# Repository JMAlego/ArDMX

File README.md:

# ArDMX

*DMX512 Interface Shield*

## Introduction

Following the creation of [AVR-DMX](https://github.com/JMAlego/AVR-DMX) for Arduino, I decided that my first foray into circuit board design should be the creation of a shield to work with AVR-DMX to allow proper interfacing of an Arduino to a DMX network.

**NB**: I have yet to actually get one of these made so who knows if it works, it's based on a perfboarded design that works correctly though.

## DIP Switches

- 120Ω Termination:
- Mode (only enable one unless you want a short):
  - Always Receive: Pull-down
  - Always Transmit: Pull-up
  - Software Control: Connect to pin 2
- Read Enable: Connect read output to pin 8
- Status LED Enable: Connect status LED to pin 9

## Optional Components

- D2 & D3 are only required for max voltage clamping on the DMX bus, if you're not worried about over/under-voltage then don't bother with them.
- SW2 & R1 are optional if you don't want 120Ω termination.
- J2 is not required if you don't want to use the outputs without the XLR connector.
- J1 is not required if you plan to use J2 to connect to the DMX network.
- Smoothing caps C1 & C2 are also optional if you're sure your input supply will be sufficiently smooth.
- D4 & R5 are optional if you don't want the power LED.
- Similarly, D1 & R4 are optional if you don't want the status LED.

## Rough Costing

It should be possible to build for around £10 or less (though you may need to make a few). You'll find the most expensive part is the Neutrik NC5FAH-DA (or compatible) XLR 5-pin connector.

As of revision 1.1 a cheaper option of using the 3-pin XLR Neutrik NC3FAH1-DA connector which the board now also supports.

## License

Hardware designs are licensed under the [Creative Commons Attribution 4.0 International Licence](https://creativecommons.org/licenses/by/4.0/).

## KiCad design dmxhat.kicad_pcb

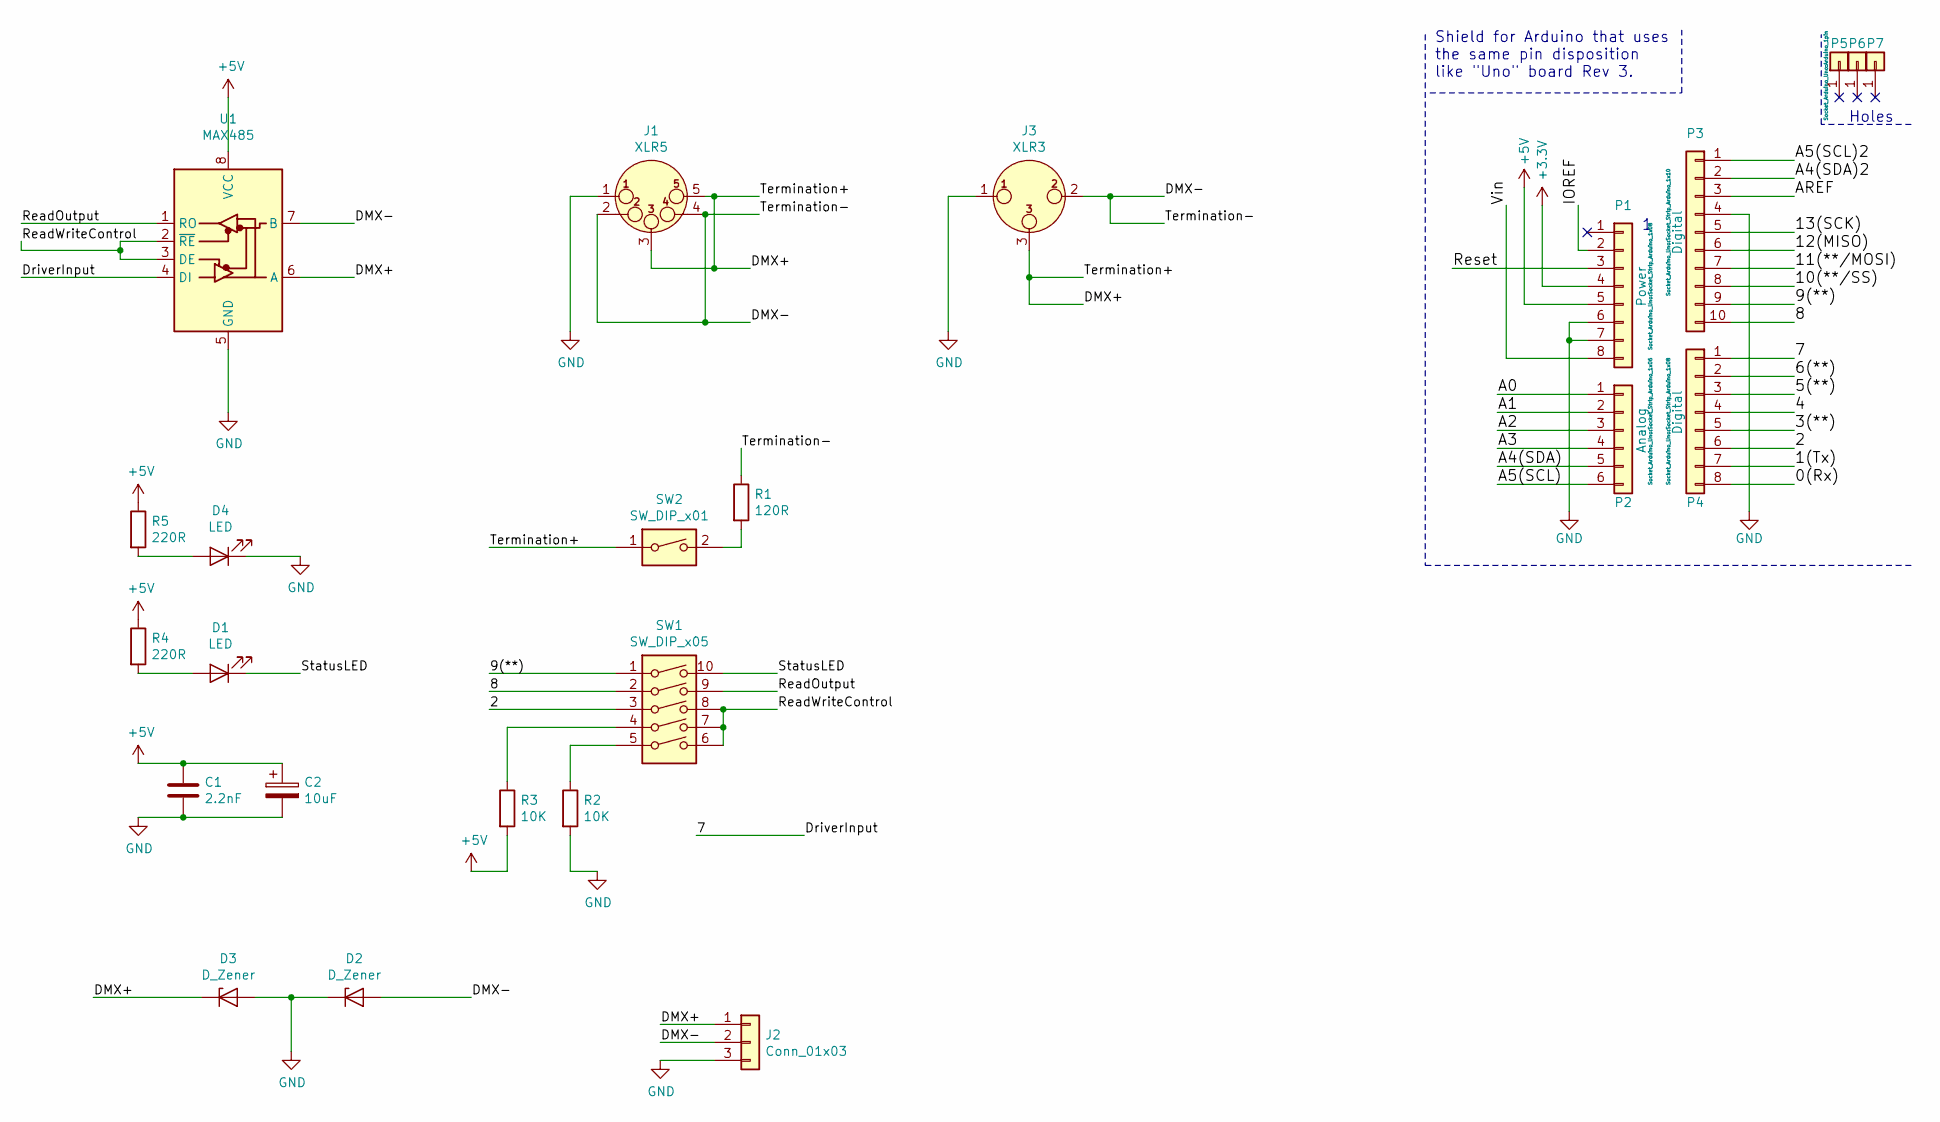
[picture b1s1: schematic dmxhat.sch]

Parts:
C1: 2.2nF; C_Disc_D5.0mm_W2.5mm_P5.00mm
C2: 10uF; CP_Radial_D5.0mm_P2.50mm
D1, D4: LED; LED_D3.0mm
D2, D3: D_Zener; D_5W_P12.70mm_Horizontal
J1: XLR5; Jack_XLR_Neutrik_NC5FAH-DA_Horizontal
J2: Conn_01x03; PinHeader_1x03_P2.54mm_Vertical
J3: XLR3; Jack_XLR_Neutrik_NC3FAH1-DA_Horizontal
P1: Power; Socket_Strip_Arduino_1x08
P2: Analog; Socket_Strip_Arduino_1x06
P3: Digital; Socket_Strip_Arduino_1x10
P4: Digital; Socket_Strip_Arduino_1x08
P5, P6, P7: CONN_01X01; Arduino_1pin
R1: 120R; R_Axial_DIN0207_L6.3mm_D2.5mm_P10.16mm_Horizontal
R2, R3: 10K; R_Axial_DIN0207_L6.3mm_D2.5mm_P10.16mm_Horizontal
R4, R5: 220R; R_Axial_DIN0207_L6.3mm_D2.5mm_P10.16mm_Horizontal
SW1: SW_DIP_x05; SW_DIP_SPSTx05_Slide_9.78x14.88mm_W7.62mm_P2.54mm
SW2: SW_DIP_x01; SW_DIP_SPSTx01_Slide_9.78x4.72mm_W7.62mm_P2.54mm
U1: MAX485; DIP-8_W7.62mm

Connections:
+3V3: P1.4
+5V: C1.1, C2.1, P1.5, R3.2, R4.1, R5.1, U1.8 (VCC)
/0(Rx): P4.8
/1(Tx): P4.7
/2: P4.6, SW1.3
/3(**): P4.5
/4: P4.4
/5(**): P4.3
/6(**): P4.2
/7: P4.1, U1.4 (DI)
/8: P3.10, SW1.2
/9(**): P3.9, SW1.1
/10(**/SS): P3.8
/11(**/MOSI): P3.7
/12(MISO): P3.6
/13(SCK): P3.5
/A0: P2.1
/A1: P2.2
/A2: P2.3
/A3: P2.4
/A4(SDA): P2.5
/A4(SDA)2: P3.2
/A5(SCL): P2.6
/A5(SCL)2: P3.1
/AREF: P3.3
/DMX+: D3.1 (K), J1.3, J1.5, J2.1, J3.3, SW2.1, U1.6 (A)
/DMX-: D2.2 (A), J1.2, J1.4 (P3), J2.2, J3.2, R1.1, U1.7 (B)
/IOREF: P1.2
/ReadOutput: SW1.9, U1.1 (RO)
/ReadWriteControl: SW1.6, SW1.7, SW1.8, U1.2 (~RE), U1.3 (DE)
/Reset: P1.3
/StatusLED: D1.1 (K), SW1.10
/Vin: P1.8
GND: C1.2, C2.2, D2.1 (K), D3.2 (A), D4.1 (K), J1.1, J1.G, J2.3, J3.1, P1.6, P1.7, P3.4, R2.2, U1.5 (GND)
unnamed: D1.2 (A), R4.2
unnamed: D4.2 (A), R5.2
unnamed: R1.2, SW2.2
unnamed: R2.1, SW1.5
unnamed: R3.1, SW1.4

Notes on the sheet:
Holes
Shield for Arduino that uses the same pin disposition like "Uno" board Rev 3.

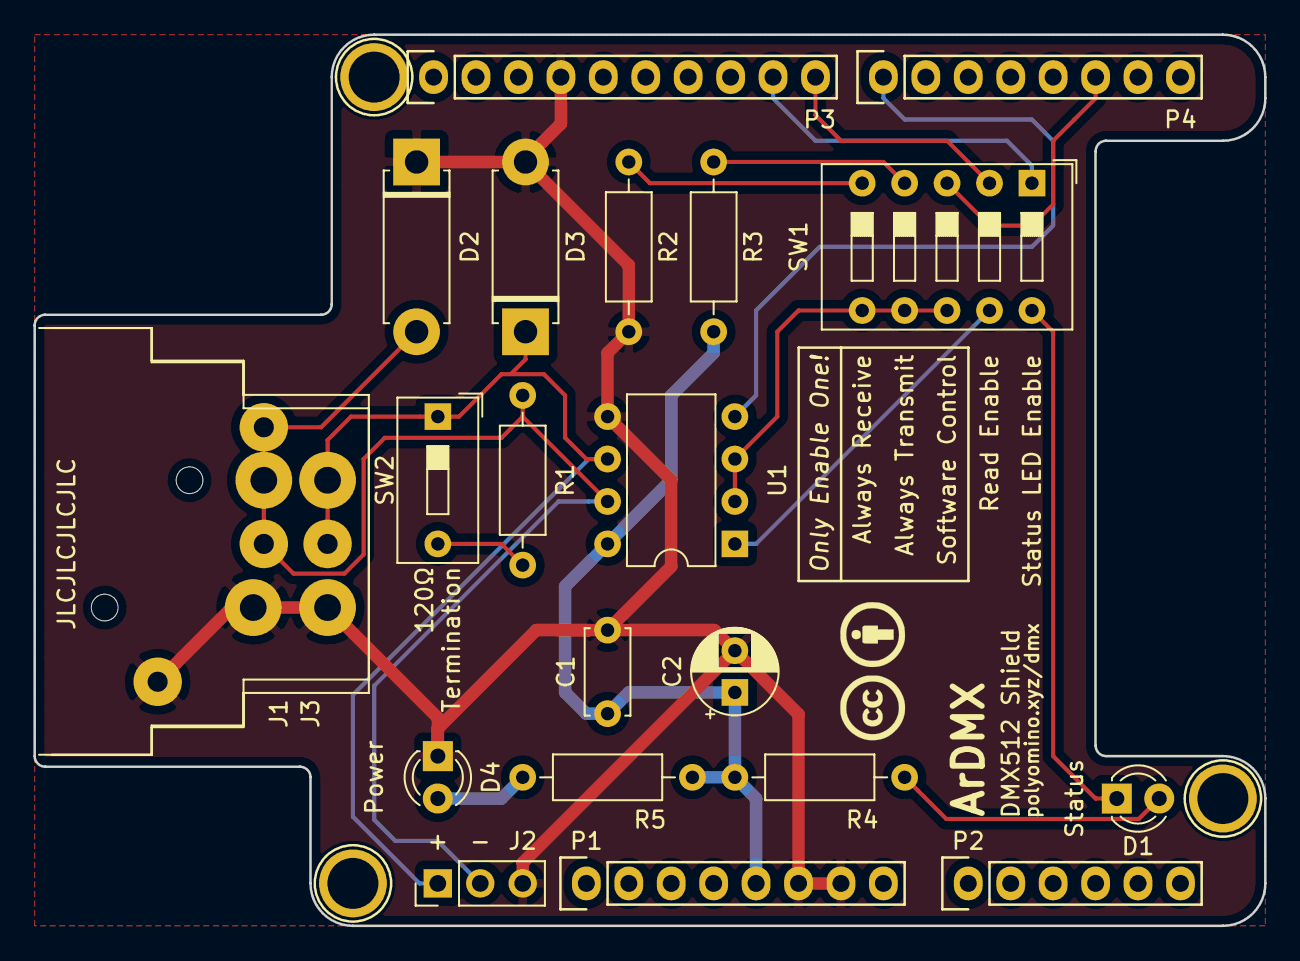
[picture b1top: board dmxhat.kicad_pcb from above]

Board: 2 copper layers, 73.7 x 53.3 mm, 24 parts (0 on the bottom side), 16 nets.

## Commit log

2020-05-30 Add license
2020-05-30 Updated Gerbers
2020-05-30 Fix silk screen
